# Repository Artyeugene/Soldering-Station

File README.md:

# Soldering-Station
Паяльная станция на жалах HAKKO T12 ver2.0

Atmega328p (фьюзы - default), индикация на MAX7219, управление - энкодер

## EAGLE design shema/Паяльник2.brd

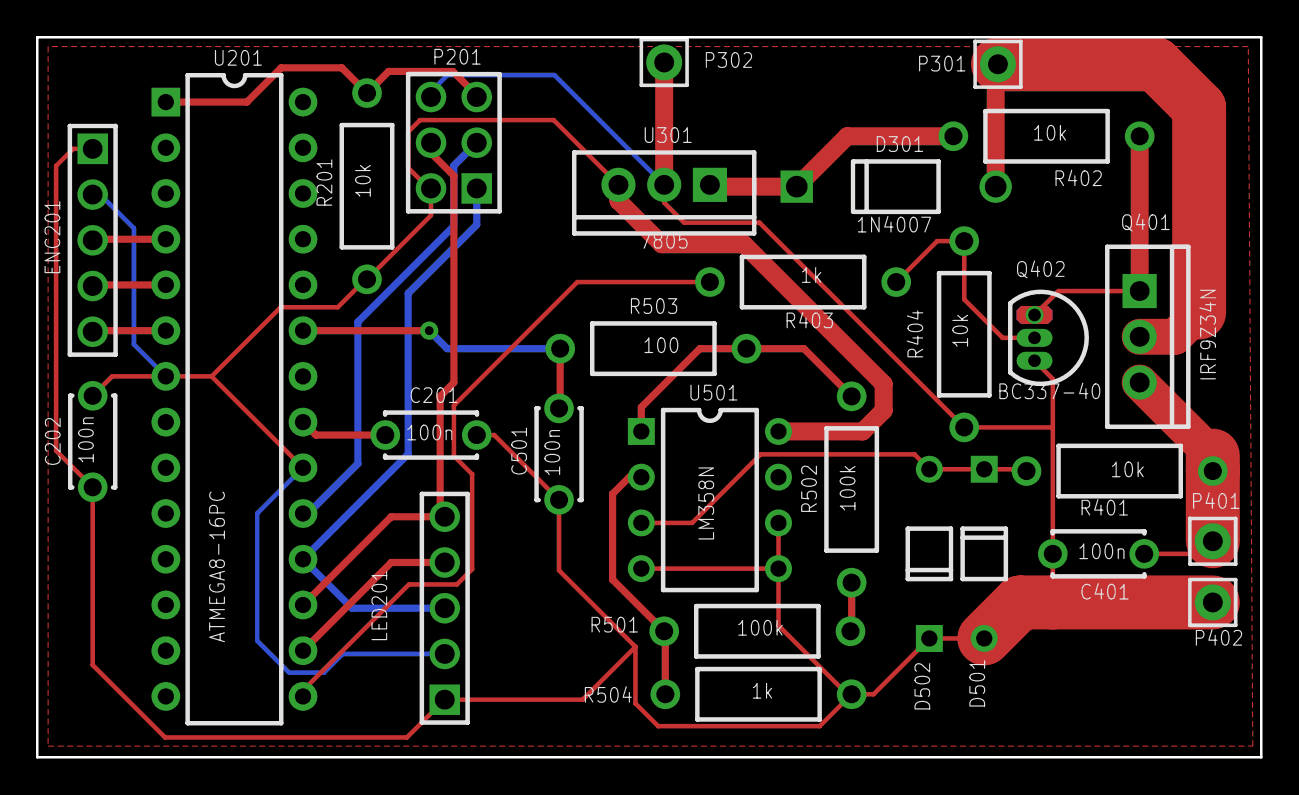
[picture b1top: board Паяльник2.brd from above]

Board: 2 copper layers, 68.0 x 40.0 mm, 28 parts (0 on the bottom side), 22 nets.

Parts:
C201, C401: 100n; CAP-5.08/5.1x2.5
C202, C501: 100n; CAP-5.08/5.1x2.5_C202
D301: 1N4007; DO-41
D501, D502: DIODE-10MM; R-1
ENC201: 644456-5; HDR-1x5T/2.54/12x2
LED201: 644456-5; HDR-1x5T/2.54/12x2
P201: 3X2_PIN_VERT; HDR-2x3T/2.54x2.54/8x5
P301, P302: CON_1PIN; 1PIN
P401: Zhalo; 1PIN
P402: GND; 1PIN
Q401: IRF9Z34N; TO-220
Q402: BC337-40; TO-92
R201, R404: 10k; RES-10.35/6.8x2.8
R401, R402: 10k; RES-10.35/6.8x2.8_R401
R403, R504: 1k; RES-10.35/6.8x2.8_R401
R501: 100k; RES-10.35/6.8x2.8_R401
R502: 100k; RES-10.35/6.8x2.8
R503: 100; RES-10.35/6.8x2.8_R401
U201: ATMEGA8-16PC; DIP-28
U301: 7805; TO-220_U301
U501: LM358N; DIP-8

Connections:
+5V: C202.2, ENC201.2, LED201.2, P201.2, R201.2, U201.7, U201.20, U301.3, U501.8
+25V: D301.2, P301.1, Q401.2
+25V_D: D301.1, R402.2, U301.1
Clk: LED201.4, U201.16
GND_A: C201.1, C202.1, C401.1, C501.1, D501.2, D502.1, ENC201.1, LED201.1, P201.6, P302.1, P402.1, Q402.3, R404.1, R504.1, U301.2, U501.4, U501.5, U501.6
LM358-analog: C501.2, R503.2, U201.23
Miso: LED201.3, P201.1, U201.18
Mosi: LED201.5, P201.4, U201.17
Net_4: Q401.1, Q402.1, R402.1
Net_6: Q402.2, R403.2, R404.2
Net_17: C401.2, P401.1, Q401.3, R401.1
Net_19: R501.1, R504.2, U501.2
Net_20: R502.2, R503.1, U501.1
PWM: R403.1, U201.15
Reset: P201.5, R201.1, U201.1
Sck: P201.3, U201.19
Tip_S: D501.1, D502.2, R401.2, U501.3
Сеть_3: ENC201.3, U201.4
Сеть_4: ENC201.4, U201.5
Сеть_5: ENC201.5, U201.6
Сеть_24: R501.2, R502.1
Сеть_27: C201.2, U201.21

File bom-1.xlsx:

# | Метка | Значение | Имя | Производитель | Количество
1 | C201_T12-CPU, C202_T12-CPU, C401_T12-MOSFET, C501_ANALOG-LM358 | 100n | CAP_5MM |  | 4
2 | D301_POWER-T12 |  | 1N4007 |  | 1
3 | D501_ANALOG-LM358, D502_ANALOG-LM358 |  | DIODE-10MM |  | 2
4 | ENC201_T12-CPU, LED201_T12-CPU |  | 644456-5 |  | 2
5 | P201_T12-CPU |  | 3X2_PIN_VERT |  | 1
6 | P301_POWER-T12, P302_POWER-T12 |  | CON_1PIN |  | 2
7 | P401_T12-MOSFET | Zhalo | CON_1PIN |  | 1
8 | P402_T12-MOSFET | GND | CON_1PIN |  | 1
9 | Q401_T12-MOSFET |  | IRF9Z34N |  | 1
10 | Q402_T12-MOSFET |  | BC337-40 |  | 1
11 | R201_T12-CPU | 10k | RES-250MW |  | 1
12 | R401_T12-MOSFET, R402_T12-MOSFET, R404_T12-MOSFET | 10k | RES-250MW_2 |  | 3
13 | R403_T12-MOSFET | 1k | RES-250MW |  | 1
14 | R501_ANALOG-LM358, R502_ANALOG-LM358 | 100k | RES-250MW |  | 2
15 | R503_ANALOG-LM358 | 100 | RES-250MW |  | 1
16 | R504_ANALOG-LM358 | 1k | RES-250MW_2 |  | 1
17 | U201_T12-CPU |  | ATMEGA328 |  | 1
18 | U301_POWER-T12 |  | 7805 |  | 1
19 | U501_ANALOG-LM358 |  | LM358N |  | 1
